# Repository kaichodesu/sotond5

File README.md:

# sotond5
remake /lcdlib if updated
remake /mainsreq if updated

compilation
avr-gcc -mmcu=atmega644p -Llcdlib -o main.hex main.c -llcd

flashing
sudo avrdude -c usbasp -p m644p -U flash:w:main.hex

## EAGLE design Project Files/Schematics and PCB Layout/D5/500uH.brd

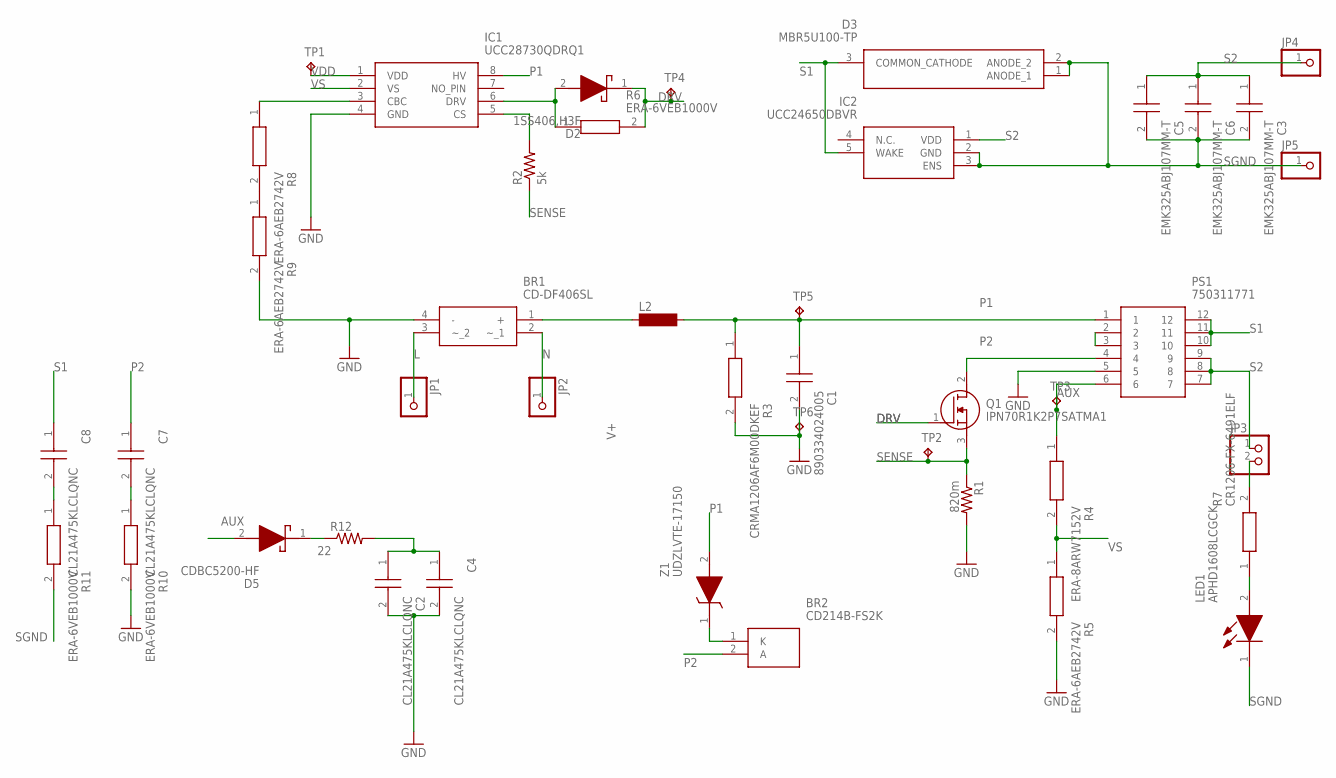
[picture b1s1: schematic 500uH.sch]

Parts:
BR1: CD-DF406SL; CDDF406SL
BR2: CD214B-FS2K; CD214BFS2K
C1: 890334024005
C2, C4, C7, C8: CL21A475KLCLQNC; CAPC2012X95N
C3, C5, C6: EMK325ABJ107MM-T; CAPC3225X270N
D2: 1SS406,H3F; SOD2513X115N
D3: MBR5U100-TP; MBR5U100TP
D5: CDBC5200-HF; DIOM8059X290N
IC1: UCC28730QDRQ1; SOIC127P600X175-8N
IC2: UCC24650DBVR; SOT95P280X145-5N
JP1, JP2, JP4, JP5: PINHD-1X1; 1X01
JP3: PINHD-1X2; 1X02
L2: MS50SRU1048-471Y; INDDFN1000X1000X480-2N
LED1: APHD1608LCGCK; LEDM168X80N
PS1: 750311771
Q1: IPN70R1K2P7SATMA1
R1: 820m; R0805
R2: 5k; R0805
R3: CRMA1206AF6M00DKEF; RESC3216X74N
R4: ERA-8ARW7152V; ERA8A_(0805)
R5, R8, R9: ERA-6AEB2742V; ERA6A_(0805)
R6, R10, R11: ERA-6VEB1000V; ERA6VK
R7: CR1206-FX-6491ELF; RESC3216X75N
R12: 22; R0805
TP1, TP2, TP3, TP4, TP5, TP6: TPB1,27; B1,27
Z1: UDZLVTE-17150; SODFL2512X90N

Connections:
AUX: D5.2 (A), PS1.6, R4.1, TP3.TP
DRV: D2.1 (K), Q1.1 (G), R6.2, TP4.TP
GND: BR1.4 (-), C1.2, C2.2, C4.2, IC1.4 (GND), PS1.5, R1.2, R3.2, R5.2, R9.2, R10.2, TP6.TP
L: BR1.3 (~_2), JP1.1
N: BR1.2 (~_1), JP2.1
unnamed: IC1.5 (CS), R2.2
unnamed: C7.2, R10.1
unnamed: C8.2, R11.1
unnamed: D5.1 (K), R12.1
unnamed: PS1.2, PS1.3
unnamed: BR2.1 (K), Z1.1 (K)
unnamed: D2.2 (A), IC1.6 (DRV), R6.1
unnamed: R8.2, R9.1
unnamed: LED1.2 (A), R7.1
unnamed: IC1.3 (CBC), R8.1
unnamed: JP3.2, R7.2
P1: C1.1, IC1.8 (HV), L2.2, PS1.1, R3.1, TP5.TP, Z1.2 (A)
P2: BR2.2 (A), C7.1, PS1.4, Q1.2 (D)
S1: C8.1, D3.3 (COMMON_CATHODE), IC2.5 (WAKE), PS1.10, PS1.11, PS1.12
S2: C3.1, C5.1, C6.1, IC2.1 (VDD), JP3.1, JP4.1, PS1.7, PS1.8, PS1.9
SENSE: Q1.3 (S), R1.1, R2.1, TP2.TP
SGND: C3.2, C5.2, C6.2, D3.1 (ANODE_1), D3.2 (ANODE_2), IC2.2 (GND), IC2.3 (ENS), JP5.1, LED1.1 (K), R11.2
V+: BR1.1 (+), L2.1
VDD: C2.1, C4.1, IC1.1 (VDD), R12.2, TP1.TP
VS: IC1.2 (VS), R4.2, R5.1

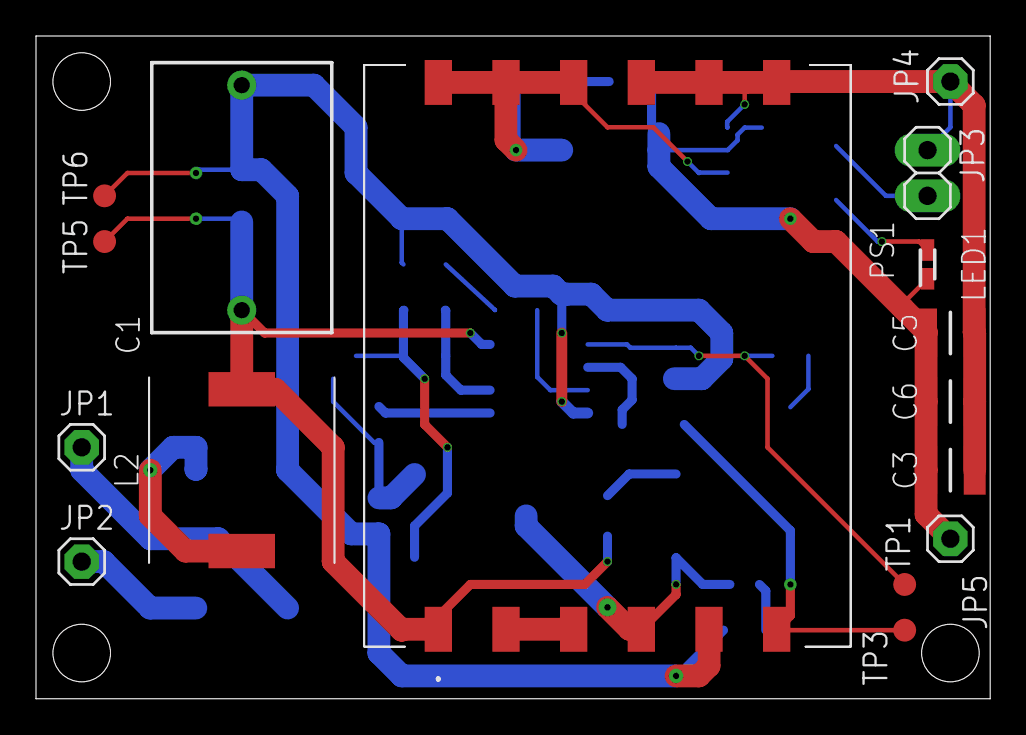
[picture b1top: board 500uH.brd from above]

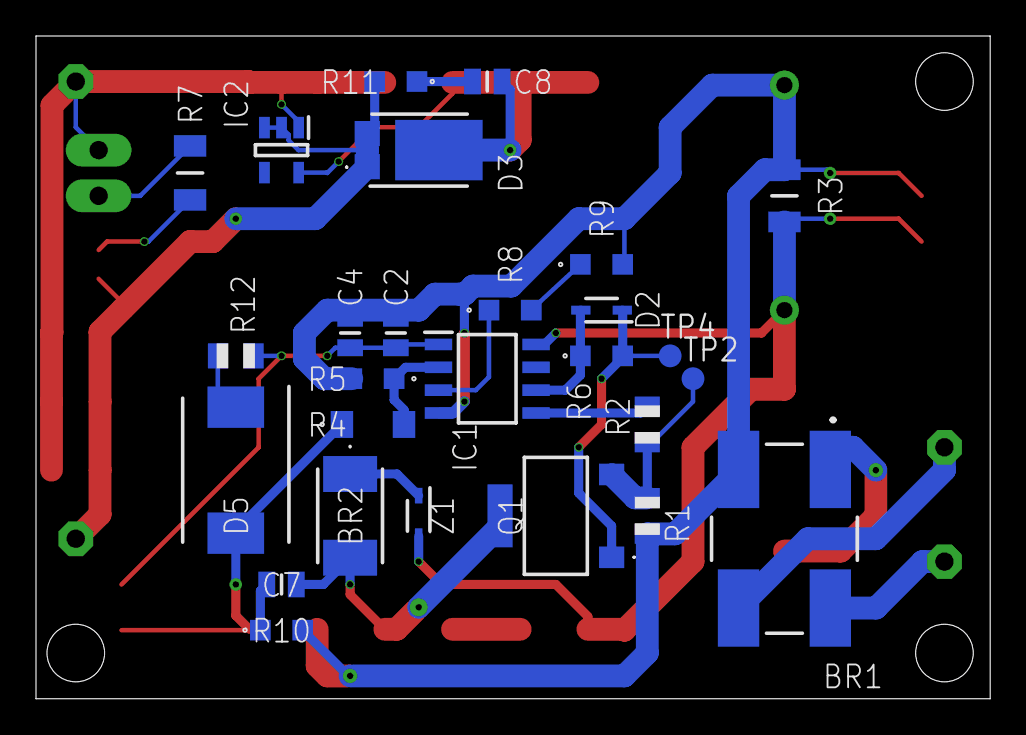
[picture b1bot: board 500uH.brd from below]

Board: 2 copper layers, 53.0 x 36.8 mm, 43 parts (27 on the bottom side), 25 nets.

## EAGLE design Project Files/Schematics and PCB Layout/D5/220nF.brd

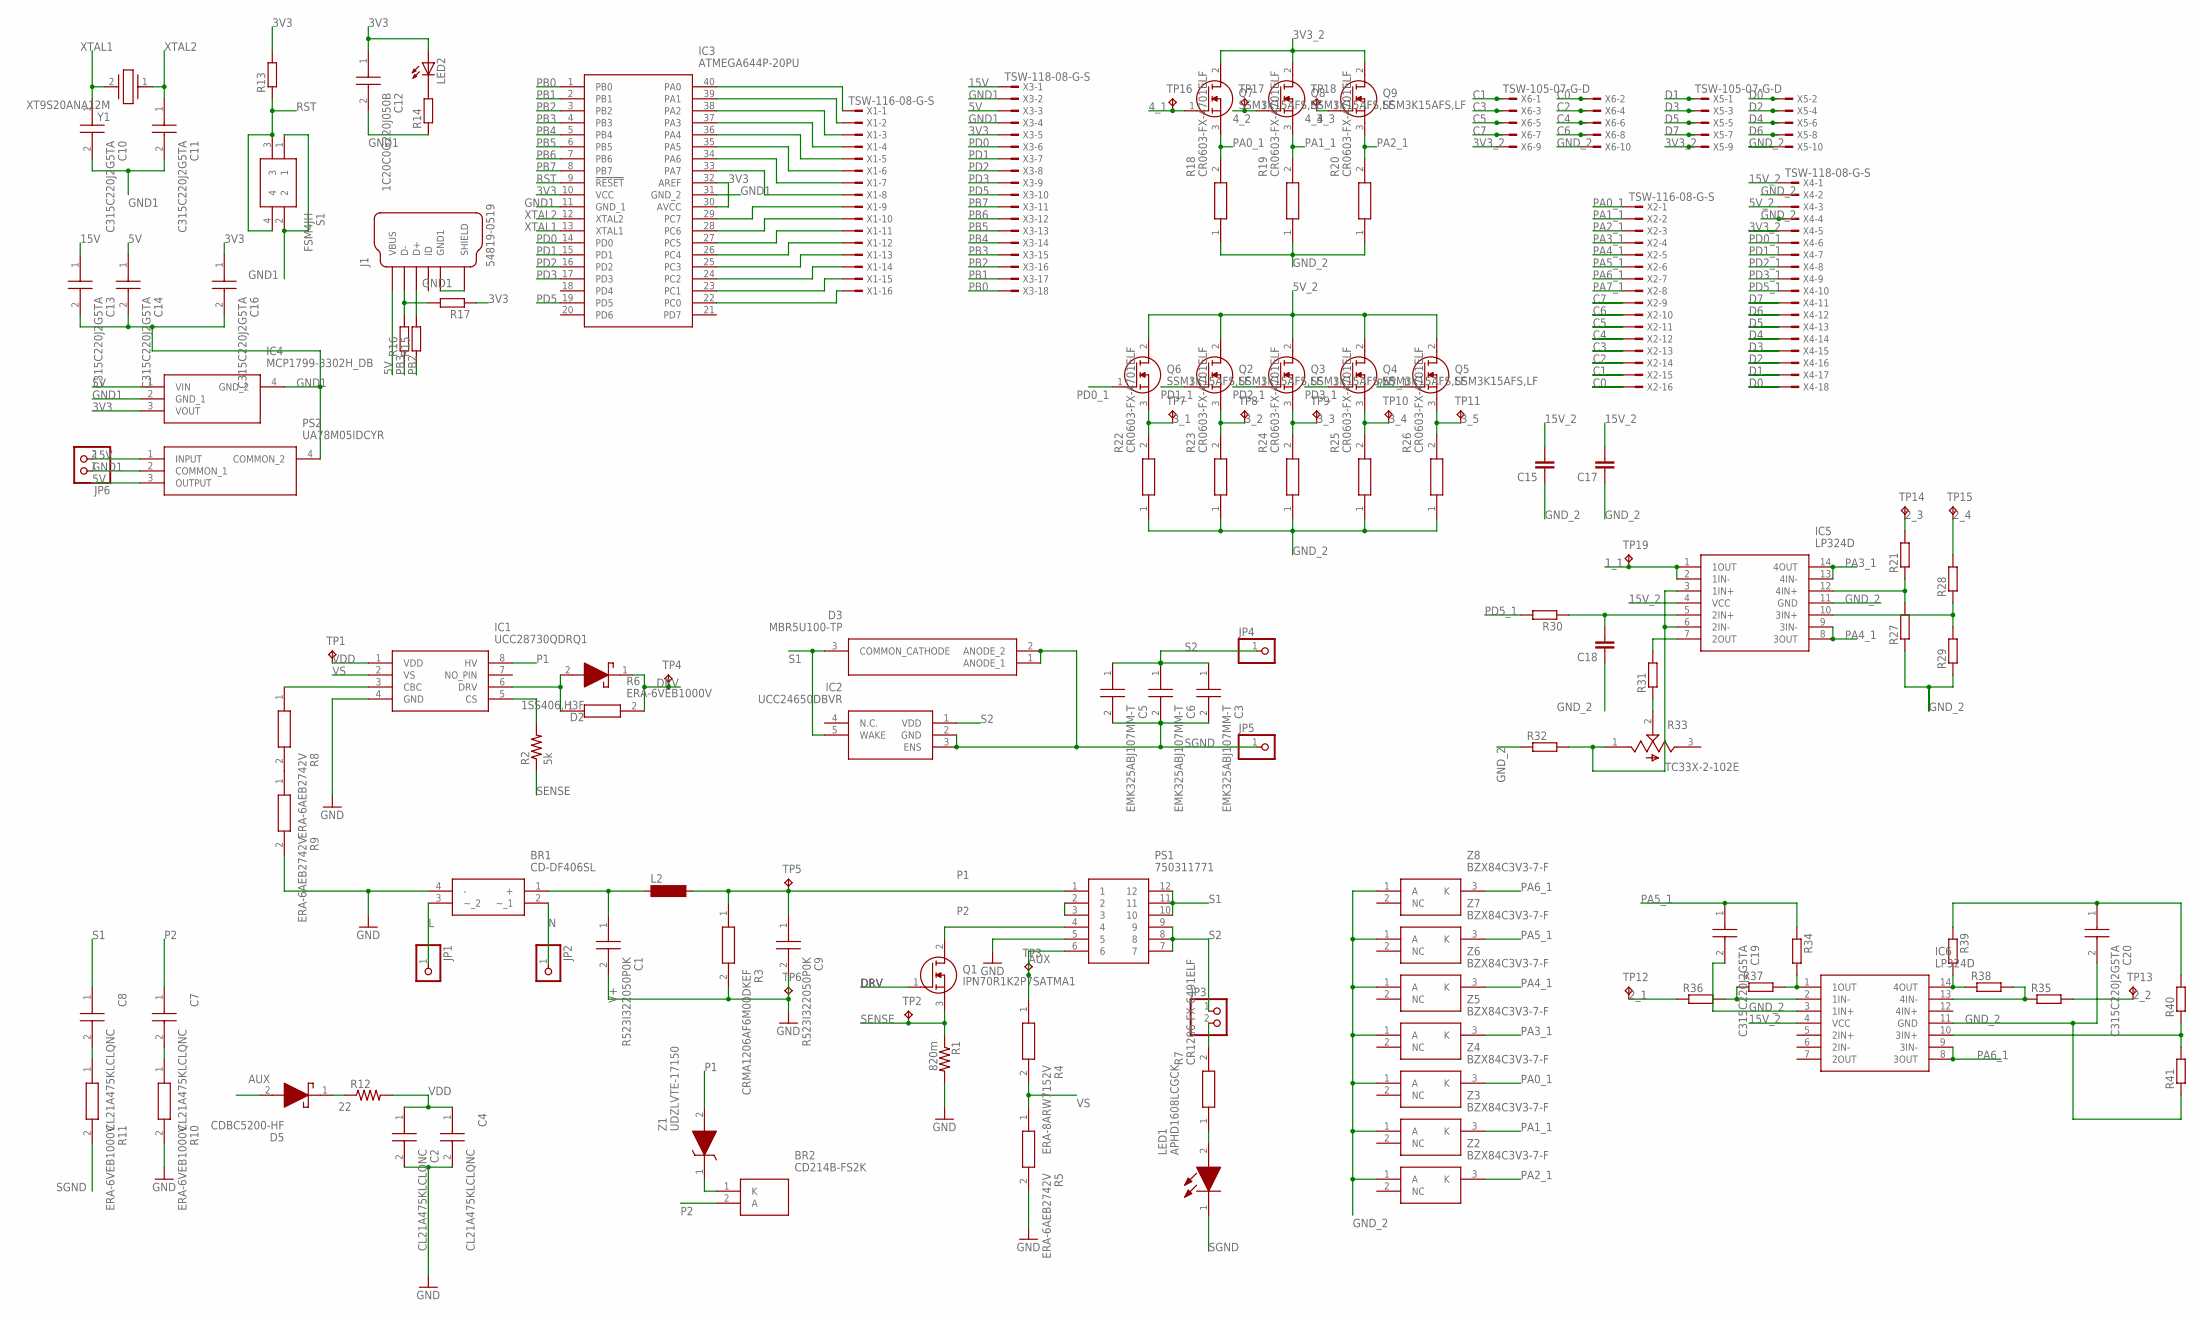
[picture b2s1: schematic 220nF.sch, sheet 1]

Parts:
BR1: CD-DF406SL; CDDF406SL
BR2: CD214B-FS2K; CD214BFS2K
C1, C9: R523I322050P0K; HDRV2W65P0X1500_1X2_1790X585X1
C2, C4, C7, C8: CL21A475KLCLQNC; CAPC2012X95N
C3, C5, C6: EMK325ABJ107MM-T; CAPC3225X270N
C10, C11, C13, C14, C16, C19, C20: C315C220J2G5TA; C315
C12: 1C20C0G220J050B
C15, C17, C18: C-EUC0805; C0805
D2: 1SS406,H3F; SOD2513X115N
D3: MBR5U100-TP; MBR5U100TP
D5: CDBC5200-HF; DIOM8059X290N
IC1: UCC28730QDRQ1; SOIC127P600X175-8N
IC2: UCC24650DBVR; SOT95P280X145-5N
IC3: ATMEGA644P-20PU; DIP1556W56P254L5232H483Q40N
IC4: MCP1799-3302H_DB; SOT230P700X180-4N
IC5, IC6: LP324D; SOIC127P600X175-14N
J1: 54819-0519; MOLEX_54819-0519
JP1, JP2, JP4, JP5: PINHD-1X1; 1X01
JP3, JP6: PINHD-1X2; 1X02
L2: MS50SRU1048-471Y; INDDFN1000X1000X480-2N
LED1: APHD1608LCGCK; LEDM168X80N
LED2: LED3MM
PS1: 750311771
PS2: UA78M05IDCYR; SOT230P700X180-4N
Q1: IPN70R1K2P7SATMA1
Q2, Q3, Q4, Q5, Q6, Q7, Q8, Q9: SSM3K15AFS,LF; SOT50P160X90-3N
R1: 820m; R0805
R2: 5k; R0805
R3: CRMA1206AF6M00DKEF; RESC3216X74N
R4: ERA-8ARW7152V; ERA8A_(0805)
R5, R8, R9: ERA-6AEB2742V; ERA6A_(0805)
R6, R10, R11: ERA-6VEB1000V; ERA6VK
R7: CR1206-FX-6491ELF; RESC3216X75N
R12: 22; R0805
R13, R14, R15, R16, R17, R34, R39: R-EU_0204/7; 0204/7
R18, R19, R20, R22, R23, R24, R25, R26: CR0603-FX-4701ELF; RESC1608X55N
R21, R27, R28, R29, R30, R31, R32, R35, R36, R37, R38, R40, R41: R-EU_R0805; R0805
R33: TC33X-2-102E; TRIM_TC33X-2-102E
S1: FSM4JH
TP1, TP2, TP3, TP4, TP5, TP6, TP7, TP8, TP9, TP10, TP11, TP12, TP13, TP14, TP15, TP16, TP17, TP18, TP19: TPB1,27; B1,27
X1, X2: TSW-116-08-G-S; TSW-116-XX-G-S
X3, X4: TSW-118-08-G-S; TSW-118-XX-G-S
X5, X6: TSW-105-07-G-D; TSW-105-XX-G-D
Y1: XT9S20ANA12M
Z1: UDZLVTE-17150; SODFL2512X90N
Z2, Z3, Z4, Z5, Z6, Z7, Z8: BZX84C3V3-7-F; SOT96P240X120-3N

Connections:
1_1: IC5.1 (1OUT), IC5.2 (1IN-), TP19.TP
2_1: R36.1, TP12.TP
2_2: R35.2, TP13.TP
2_3: R21.2, TP14.TP
2_4: R28.2, TP15.TP
3V3: C12.1, C16.1, IC3.10 (VCC), IC3.30 (AVCC), IC3.32 (AREF), IC4.3 (VOUT), LED2.A, R13.2, R17.1, X3.5
3V3_2: Q7.2 (D), Q8.2 (D), Q9.2 (D), X4.5, X5.9, X6.9
3_1: Q6.3 (S), R22.2, TP7.TP
3_2: Q2.3 (S), R23.2, TP8.TP
3_3: Q3.3 (S), R24.2, TP9.TP
3_4: Q4.3 (S), R25.2, TP10.TP
3_5: Q5.3 (S), R26.2, TP11.TP
4_1: Q7.1 (G), TP16.TP
4_2: Q8.1 (G), TP17.TP
4_3: Q9.1 (G), TP18.TP
5V: C14.1, IC4.1 (VIN), J1.1 (VBUS), J1.6 (VBUS), PS2.3 (OUTPUT), X3.3
5V_2: Q2.2 (D), Q3.2 (D), Q4.2 (D), Q5.2 (D), Q6.2 (D), X4.3
15V: C13.1, JP6.2, PS2.1 (INPUT), X3.1
15V_2: C15.2, C17.2, IC5.4 (VCC), IC6.4 (VCC), X4.1
AUX: D5.2 (A), PS1.6, R4.1, TP3.TP
C0: X2.16, X6.2
C1: X2.15, X6.1
C2: X2.14, X6.4
C3: X2.13, X6.3
C4: X2.12, X6.6
C5: X2.11, X6.5
C6: X2.10, X6.8
C7: X2.9, X6.7
D0: X4.18, X5.2
D1: X4.17, X5.1
D2: X4.16, X5.4
D3: X4.15, X5.3
D4: X4.14, X5.6
D5: X4.13, X5.5
D6: X4.12, X5.8
D7: X4.11, X5.7
DRV: D2.1 (K), Q1.1 (G), R6.2, TP4.TP
GND: BR1.4 (-), C1.2, C2.2, C4.2, C9.2, IC1.4 (GND), PS1.5, R1.2, R3.2, R5.2, R9.2, R10.2, TP6.TP
GND1: C10.2, C11.2, C12.2, C13.2, C14.2, C16.2, IC3.11 (GND_1), IC3.31 (GND_2), IC4.2 (GND_1), IC4.4 (GND_2), J1.5 (GND1), J1.10 (GND1), J1.11 (SHIELD), J1.12 (SHIELD), J1.S1 (SHIELD), J1.S2 (SHIELD), JP6.1, PS2.2 (COMMON_1), PS2.4 (COMMON_2), R14.1, S1.1, S1.2, X3.2, X3.4
GND_2: C15.1, C17.1, C18.1, C19.2, C20.2, IC5.11 (GND), IC6.3 (1IN+), IC6.11 (GND), R18.1, R19.1, R20.1, R22.1, R23.1, R24.1, R25.1, R26.1, R27.1, R29.1, R32.1, R41.1, X4.2, X4.4, X5.10, X6.10, Z2.1 (A), Z3.1 (A), Z4.1 (A), Z5.1 (A), Z6.1 (A), Z7.1 (A), Z8.1 (A)
L: BR1.3 (~_2), JP1.1
N: BR1.2 (~_1), JP2.1
unnamed: IC1.5 (CS), R2.2
unnamed: C7.2, R10.1
unnamed: C8.2, R11.1
unnamed: D5.1 (K), R12.1
unnamed: PS1.2, PS1.3
unnamed: BR2.1 (K), Z1.1 (K)
unnamed: D2.2 (A), IC1.6 (DRV), R6.1
unnamed: R8.2, R9.1
unnamed: LED1.2 (A), R7.1
unnamed: IC1.3 (CBC), R8.1
unnamed: JP3.2, R7.2
unnamed: IC3.40 (PA0), X1.1
unnamed: IC3.39 (PA1), X1.2
unnamed: IC3.38 (PA2), X1.3
unnamed: IC3.37 (PA3), X1.4
unnamed: IC3.36 (PA4), X1.5
unnamed: IC3.35 (PA5), X1.6
unnamed: IC3.34 (PA6), X1.7
unnamed: IC3.33 (PA7), X1.8
unnamed: IC3.22 (PC0), X1.16
unnamed: IC3.23 (PC1), X1.15
unnamed: IC3.24 (PC2), X1.14
unnamed: IC3.25 (PC3), X1.13
unnamed: IC3.26 (PC4), X1.12
unnamed: IC3.27 (PC5), X1.11
unnamed: IC3.28 (PC6), X1.10
unnamed: IC3.29 (PC7), X1.9
unnamed: LED2.K (C), R14.2
unnamed: J1.3 (D+), J1.8 (D+), R15.2
unnamed: J1.2 (D-), J1.7 (D-), R16.2, R17.2
unnamed: C18.2, IC5.5 (2IN+), R30.1
unnamed: IC5.7 (2OUT), R31.2
unnamed: IC5.12 (4IN+), R21.1, R27.2
unnamed: IC5.10 (3IN+), R28.1, R29.2
unnamed: IC5.3 (1IN+), IC5.6 (2IN-), R32.2, R33.1 (CCW)
unnamed: R31.1, R33.2 (W)
unnamed: IC6.14 (4OUT), R38.1, R39.2
unnamed: IC6.13 (4IN-), R35.1, R38.2
unnamed: IC6.2 (1IN-), R36.2, R37.1
unnamed: IC6.1 (1OUT), R34.2, R37.2
unnamed: C20.1, R39.1, R40.2
unnamed: IC6.10 (3IN+), R40.1, R41.2
P1: C9.1, IC1.8 (HV), L2.2, PS1.1, R3.1, TP5.TP, Z1.2 (A)
P2: BR2.2 (A), C7.1, PS1.4, Q1.2 (D)
PA0_1: Q7.3 (S), R18.2, X2.1, Z4.3 (K)
PA1_1: Q8.3 (S), R19.2, X2.2, Z3.3 (K)
PA2_1: Q9.3 (S), R20.2, X2.3, Z2.3 (K)
PA3_1: IC5.13 (4IN-), IC5.14 (4OUT), X2.4, Z5.3 (K)
PA4_1: IC5.8 (3OUT), IC5.9 (3IN-), X2.5, Z6.3 (K)
PA5_1: C19.1, R34.1, X2.6, Z7.3 (K)
PA6_1: IC6.8 (3OUT), IC6.9 (3IN-), X2.7, Z8.3 (K)
PA7_1: Q5.1 (G), X2.8
PB0: IC3.1 (PB0), X3.18
PB1: IC3.2 (PB1), X3.17
PB2: IC3.3 (PB2), R15.1, X3.16
PB3: IC3.4 (PB3), R16.1, X3.15
PB4: IC3.5 (PB4), X3.14
PB5: IC3.6 (PB5), X3.13
PB6: IC3.7 (PB6), X3.12
PB7: IC3.8 (PB7), X3.11
PD0: IC3.14 (PD0), X3.6
PD0_1: Q6.1 (G), X4.6
PD1: IC3.15 (PD1), X3.7
PD1_1: Q2.1 (G), X4.7
PD2: IC3.16 (PD2), X3.8
PD2_1: Q3.1 (G), X4.8
PD3: IC3.17 (PD3), X3.9
PD3_1: Q4.1 (G), X4.9
PD5: IC3.19 (PD5), X3.10
PD5_1: R30.2, X4.10
RST: IC3.9 (!RESET), R13.1, S1.3, S1.4
S1: C8.1, D3.3 (COMMON_CATHODE), IC2.5 (WAKE), PS1.10, PS1.11, PS1.12
S2: C3.1, C5.1, C6.1, IC2.1 (VDD), JP3.1, JP4.1, PS1.7, PS1.8, PS1.9
SENSE: Q1.3 (S), R1.1, R2.1, TP2.TP
SGND: C3.2, C5.2, C6.2, D3.1 (ANODE_1), D3.2 (ANODE_2), IC2.2 (GND), IC2.3 (ENS), JP5.1, LED1.1 (K), R11.2
V+: BR1.1 (+), C1.1, L2.1
VDD: C2.1, C4.1, IC1.1 (VDD), R12.2, TP1.TP
VS: IC1.2 (VS), R4.2, R5.1
XTAL1: C10.1, IC3.13 (XTAL1), Y1.2
XTAL2: C11.1, IC3.12 (XTAL2), Y1.1

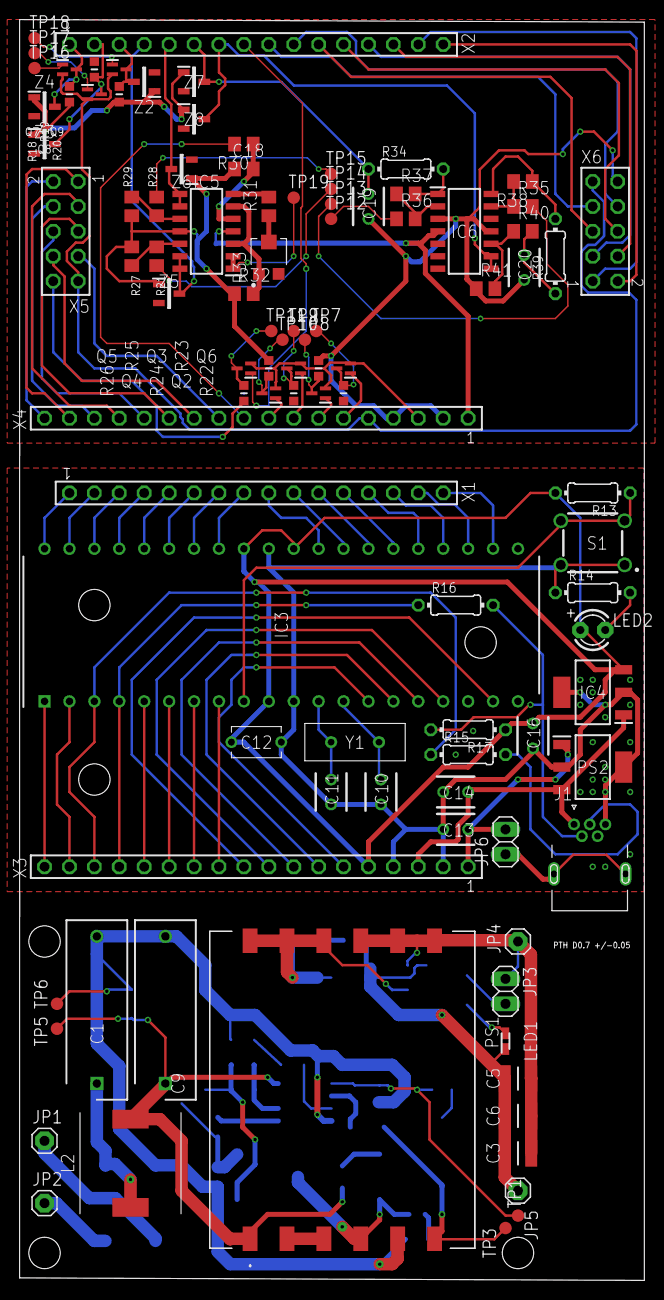
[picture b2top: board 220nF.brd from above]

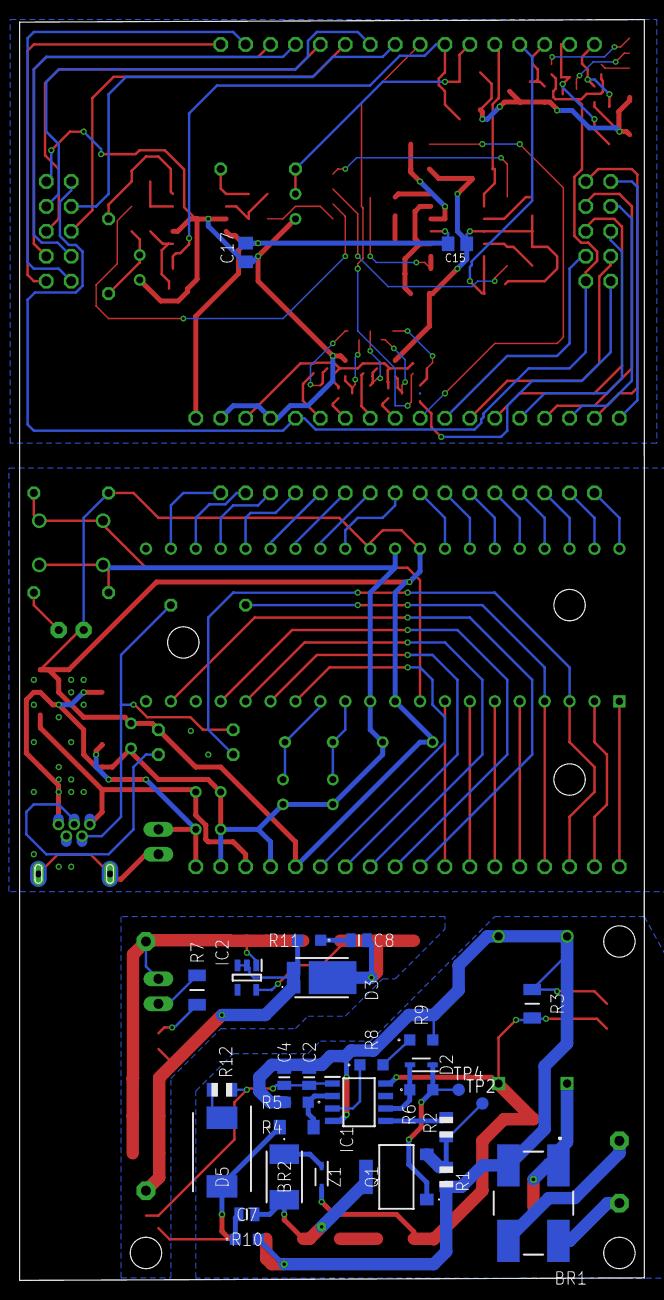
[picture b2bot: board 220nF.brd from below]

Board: 2 copper layers, 63.7 x 128.5 mm, 128 parts (29 on the bottom side), 122 nets.

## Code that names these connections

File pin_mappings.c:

/*
 * 1_1  PD5 PWM     OUT
 * 2_1  PA3 ANALOG  IN
 * 2_2  PA4 ANALOG  IN
 * 2_3  PA5 ANALOG  IN
 * 2_4  PA6 ANALOG  IN
 * 3_1  PD0 DIGITAL OUT
 * 3_2  PD1 DIGITAL OUT
 * 3_3  PD2 DIGITAL OUT
 * 3_4  PD3 DIGITAL OUT
 * 3_5  PA7 DIGITAL OUT
 * 4_1  PA0 DIGITAL IN
 * 4_2  PA1 DIGITAL IN
 * 4_3  PA2 DIGITAL IN
 */

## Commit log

2023-03-07 initial
2023-03-07 mains request
2023-03-07 mainsreq
2023-03-07 readme update
2023-03-08 graphics easter egg
2023-03-08 happiness
2023-03-09 graphics update
2023-03-09 calibration msg
2023-03-09 directory update
2023-03-09 io library
2023-03-09 gggggggg
2023-03-09 io config
2023-03-09 remove files
2023-03-09 calibration
2023-03-09 adc updates
2023-03-10 tidy
2023-03-10 syntax fix
2023-03-10 initial main completion
2023-03-10 housekeeping
2023-03-11 lib renaming
2023-03-11 adc bugfix
2023-03-11 mainsreq update
2023-03-11 font and graphics update
2023-03-11 adc phase capture fix
2023-03-11 new fonts
2023-03-11 updated main
2023-03-12 lcd loadswitch indicators
2023-03-12 fixed Fast PWM
2023-03-12 adc update
2023-03-13 improved stability
2023-03-13 updated compile instructions
2023-03-13 fixed hh8() memory addressing corruption
2023-03-13 pre-testing
2023-03-13 testbench
2023-03-13 testing
2023-03-14 attempted fix
2023-03-14 noise stability
2023-03-14 System Flowchart
2023-03-14 main.drawio
2023-03-14 system.drawio
2023-03-14 Added memory.drawio
2023-03-14 Added LCD timing.drawio
2023-03-14 Added Interrupt Service Routine.drawio
2023-03-15 Added memory allocation.drawio
2023-03-17 removing oversized files and fixing HEAD
